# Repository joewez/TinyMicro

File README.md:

TinyMicro
=========

Disclaimer: The Digispark name belongs to Digistump LLC.  I am not affiliated with them in any way. 
            BTW: Check out some great hardware at http://www.digistump.com/.  Buy something and support
            Open Hardware.

This is a simple homemade build of the Digispark hardware design.  It is not a perfect duplicate, but does keep
the basic functionality of the commercial hardware.  Besides being built with a single-sided, non-plated 
through hole PCB, there are some major differences to note:

     1. Power Supply
        This implementation provides much less power than the Digispark.
        
     2. Female Headers
        The headers do not implement the Digispark footprint.
        
     3. USB Connector
        This design uses an actual connector instead of the PCB.
        
The rest of the differences and changes are the result of what parts I could get and what skills I have for
building such things.

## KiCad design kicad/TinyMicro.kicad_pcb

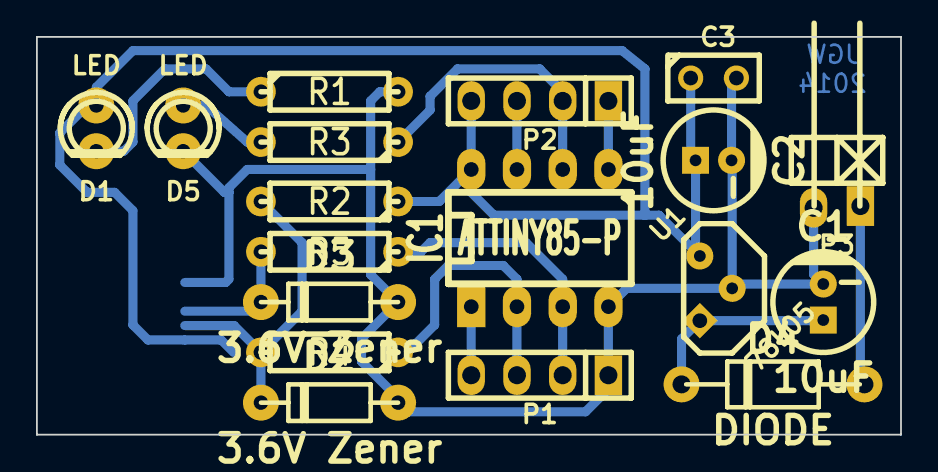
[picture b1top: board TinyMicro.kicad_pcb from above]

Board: 2 copper layers, 48.0 x 22.1 mm, 19 parts (1 on the bottom side), 14 nets.

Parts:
C1, C2: 10uF; CP_5x7mm
C3: 100nF; C1
CON1: USB-MINI-B; conn_usb_B_mini_smd
D1: LED; led_3mm_green
D2, D3: 3.6V Zener; diode_do35
D4: DIODE; diode_do41
D5: LED; led_3mm_red
IC1: ATTINY85-P; DIP-8__300_ELL
P1, P2: CONN_4; pin_socket_4
P3: CONN_2; pin_strip_2-90
R1, R3: 220ohm; R3-LARGE_PADS
R2: 1.5Kohm; R3-LARGE_PADS
R4, R5: 68ohm; R3-LARGE_PADS
U1: 78L05; TO92

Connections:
GND: C1.2, C2.2, C3.2, CON1.5, D2.1, D3.1, D5.2, IC1.4, P1.1, P3.2, R1.2, U1.2
unnamed: C1.1, D4.2, U1.1
unnamed: D4.1, P3.1
unnamed: D1.2, R1.1
unnamed: D5.1, R3.2
unnamed: CON1.3, D3.2, R5.2
unnamed: CON1.2, D2.2, R2.2, R4.2
P0: IC1.5, P2.1
P1: IC1.6, P2.2, R3.1
P2: IC1.7, P2.3
P3: IC1.2, P1.3, R4.1
P4: IC1.3, P1.2, R5.1
P5: IC1.1, P1.4
VCC: C2.1, C3.1, CON1.1, D1.1, IC1.8, P2.4, R2.1, U1.3

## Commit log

2014-06-15 Initial Load
    This is the version of my Digispark clone at the time I posted on
    digistump.com.
